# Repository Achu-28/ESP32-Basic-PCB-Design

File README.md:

# ESP32 Development Board – PCB Design

## Overview

This project involves designing a basic ESP32 Development Board using **KiCad**, an open-source electronic design automation (EDA) software.

The objective was to understand the fundamentals of PCB design, including schematic creation, component placement, PCB layout, routing and 3D visualization.

## Tools Used

- **PCB Design Software:** KiCad
- **Microcontroller Platform:** ESP32
- **Design Type:** Development Board PCB

## Project Structure

- `KiCad-Project/` – Contains the KiCad schematic, PCB layout and project files.
- `Images/` – Contains schematic, PCB layout and 3D visualization screenshots.
- `Fabrication-Files/` – Contains manufacturing files, if generated.

## Design Overview

### 1. Schematic Design

The circuit schematic was designed using KiCad to establish the electrical connections between the ESP32 and the associated components.

![Schematic Design]

### 2. PCB Layout

The PCB layout was created by arranging components and routing the required electrical connections.

![PCB Layout]

### 3. 3D Visualization

The 3D viewer in KiCad was used to visualize the final PCB design.

![3D PCB View]

## Learning Outcomes

Through this project, I gained practical experience in:

- Electronic schematic design.
- PCB component placement and routing.
- Understanding PCB design rules and clearances.
- Using KiCad for PCB development.
- Visualizing PCB designs using the 3D viewer.

## Software

KiCad – Electronic Design Automation Software.

Website: https://www.kicad.org/

## Author

[K V ACHUTHANANDA KUMAR]

B.Tech – Electronics and Communication Engineering

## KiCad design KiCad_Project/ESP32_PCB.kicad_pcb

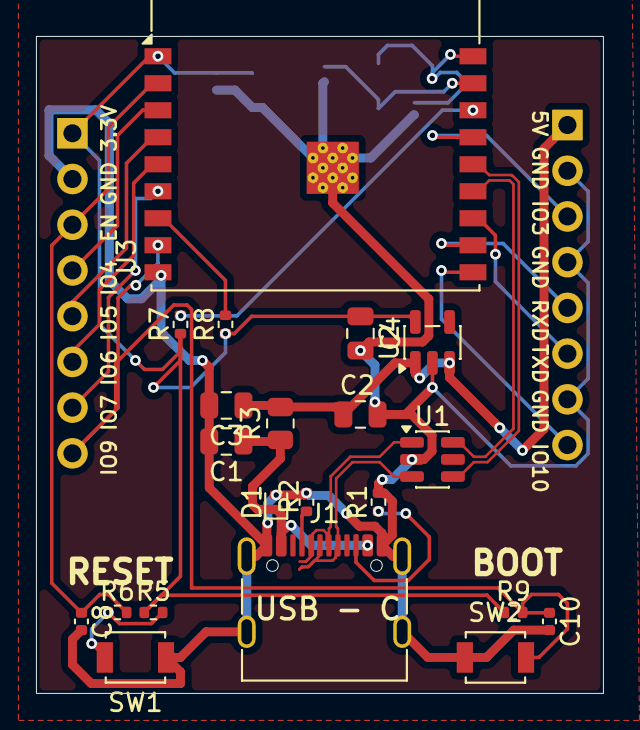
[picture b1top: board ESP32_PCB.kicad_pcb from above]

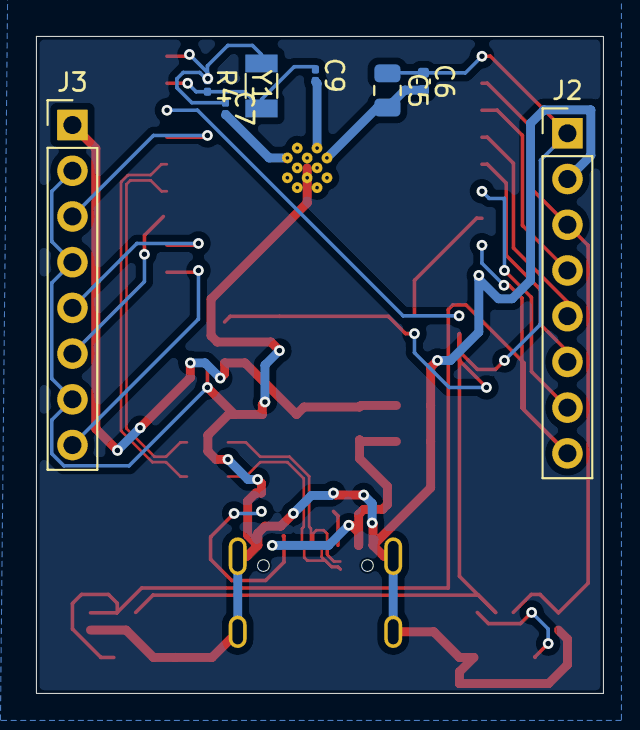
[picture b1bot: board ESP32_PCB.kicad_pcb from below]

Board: 4 copper layers, 31.5 x 36.5 mm, 29 parts (8 on the bottom side), 25 nets.

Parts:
C1, C2, C3, C4, C5: 4u7; C_0805_2012Metric
C6, C8, C10: 100n; C_0402_1005Metric
C7, C9: 4u7; C_0201_0603Metric
D1: PESD5V0L1ULD; D_SOD-882D
J1: USB_C_Receptacle_USB2.0_16P; USB_C_Receptacle_G-Switch_GT-USB-7010ASV
J2, J3: Conn_01x08_Pin; PinHeader_1x08_P2.54mm_Vertical
R1, R2: 5.1k; R_0402_1005Metric
R3: 0R; R_0805_2012Metric
R4: R; R_0201_0603Metric
R5, R7, R8, R9: 10k; R_0402_1005Metric
R6: 100R; R_0402_1005Metric
SW1, SW2: SW_Push; SW_SPST_B3U-1000P
U1: USBLC6-2SC6; SOT-23-6
U2: AP2112K-3.3; SOT-23-5
U3: ESP32-C3-WROOM-02
Y1: Crystal; Crystal_SMD_3215-2Pin_3.2x1.5mm

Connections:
3.3V: C4.1, C5.1, C6.1, J2.1, R5.1, R7.1, R8.1, R9.1, U2.5 (VOUT), U3.1 (3V3)
+5V: C2.1, C3.1, J3.1, R3.2, U2.1 (VIN), U2.3 (EN)
/ESP32/D+: J1.A6 (D+), J1.B6 (D+), U1.3 (I/O2)
/ESP32/D-: J1.A7 (D-), J1.B7 (D-), U1.1 (I/O1)
/ESP32/EN: C8.1, J2.3, R6.2, U3.2 (EN)
/ESP32/IO2: R7.2, U3.16 (IO2)
/ESP32/IO3: J3.3, U3.15 (IO3)
/ESP32/IO4: J2.4, U3.3 (IO4)
/ESP32/IO5: J2.5, U3.4 (IO5)
/ESP32/IO6: J2.6, U3.5 (IO6)
/ESP32/IO7: J2.7, U3.6 (IO7)
/ESP32/IO8: R8.2, U3.7 (IO8)
/ESP32/IO9: C10.1, J2.8, R9.2, SW2.2, U3.8 (IO9)
/ESP32/IO10: J3.8, U3.10 (IO10)
/ESP32/RXD: J3.5, U3.11 (IO20/RXD)
/ESP32/TXD: J3.6, U3.12 (IO21/TXD)
GND: C1.2, C2.2, C3.2, C4.2, C5.2, C6.2, C7.2, C8.2, C9.2, C10.2, D1.2 (A), J1.A1 (GND), J1.A12 (GND), J1.B1 (GND), J1.B12 (GND), J1.SH (SHIELD), J2.2, J3.2, J3.4, J3.7, R1.2, R2.2, SW1.1, SW2.1, U1.2 (GND), U2.2 (GND), U3.9 (GND), U3.19 (GND)
unnamed: J1.A5 (CC1), R2.1
unnamed: J1.B5 (CC2), R1.1
unnamed: R5.2, R6.1, SW1.2
unnamed: C7.1, R4.1, U3.18 (IO0), Y1.1
unnamed: C9.1, R4.2, U3.17 (IO1), Y1.2
USB_D+: U1.4 (I/O2), U3.14 (IO19)
USB_D-: U1.6 (I/O1), U3.13 (IO18)
VBUS: C1.1, D1.1 (K), J1.A4 (VBUS), J1.A9 (VBUS), J1.B4 (VBUS), J1.B9 (VBUS), R3.1
